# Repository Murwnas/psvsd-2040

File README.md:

# PSVSD 2040

This is a module based on [Yinfanlu's PSVSD adapter](https://github.com/yifanlu/psvsd/). Last year, I took the original Eagle Autodesk files and adapted them to a [KiCad EDA source](https://github.com/Murwnas/psvsd-kicad). This repo code is based on my adaptation. 

One of the problems with the original PSVSD is the out-of-production Genesys chip, which appears to be a generic USB-to-SD bridge that simply exposes Mass Storage. It's theoretically possible to use any such bridge chip in its place, but anyone who has read Yinfanlu's write-up on this will also know that power consumption is the main problem behind those adapters. The PS Vita's modem port never switches off power to the modem port. Therefore, these adapters consume power even when the console is off.

My own fun idea was to recreate this adapter using my favorite chip: The RP2040. It has a USB interface, fast GPIO lines, and very low power consumption---with the potential to go into deep-sleep-like states to draw very small amounts. 

The main downside is USB 1.1 speeds, which theoretically cap at 1.2 MB/s. 

Right now, a board has been designed and fabricated, but I have not had the time to assemble and test it. Whether this is a viable concept will remain to be seen.

Do not attempt to reproduce this unless you are fine with potentially making a faulty board that may or may not fry your PS Vita!

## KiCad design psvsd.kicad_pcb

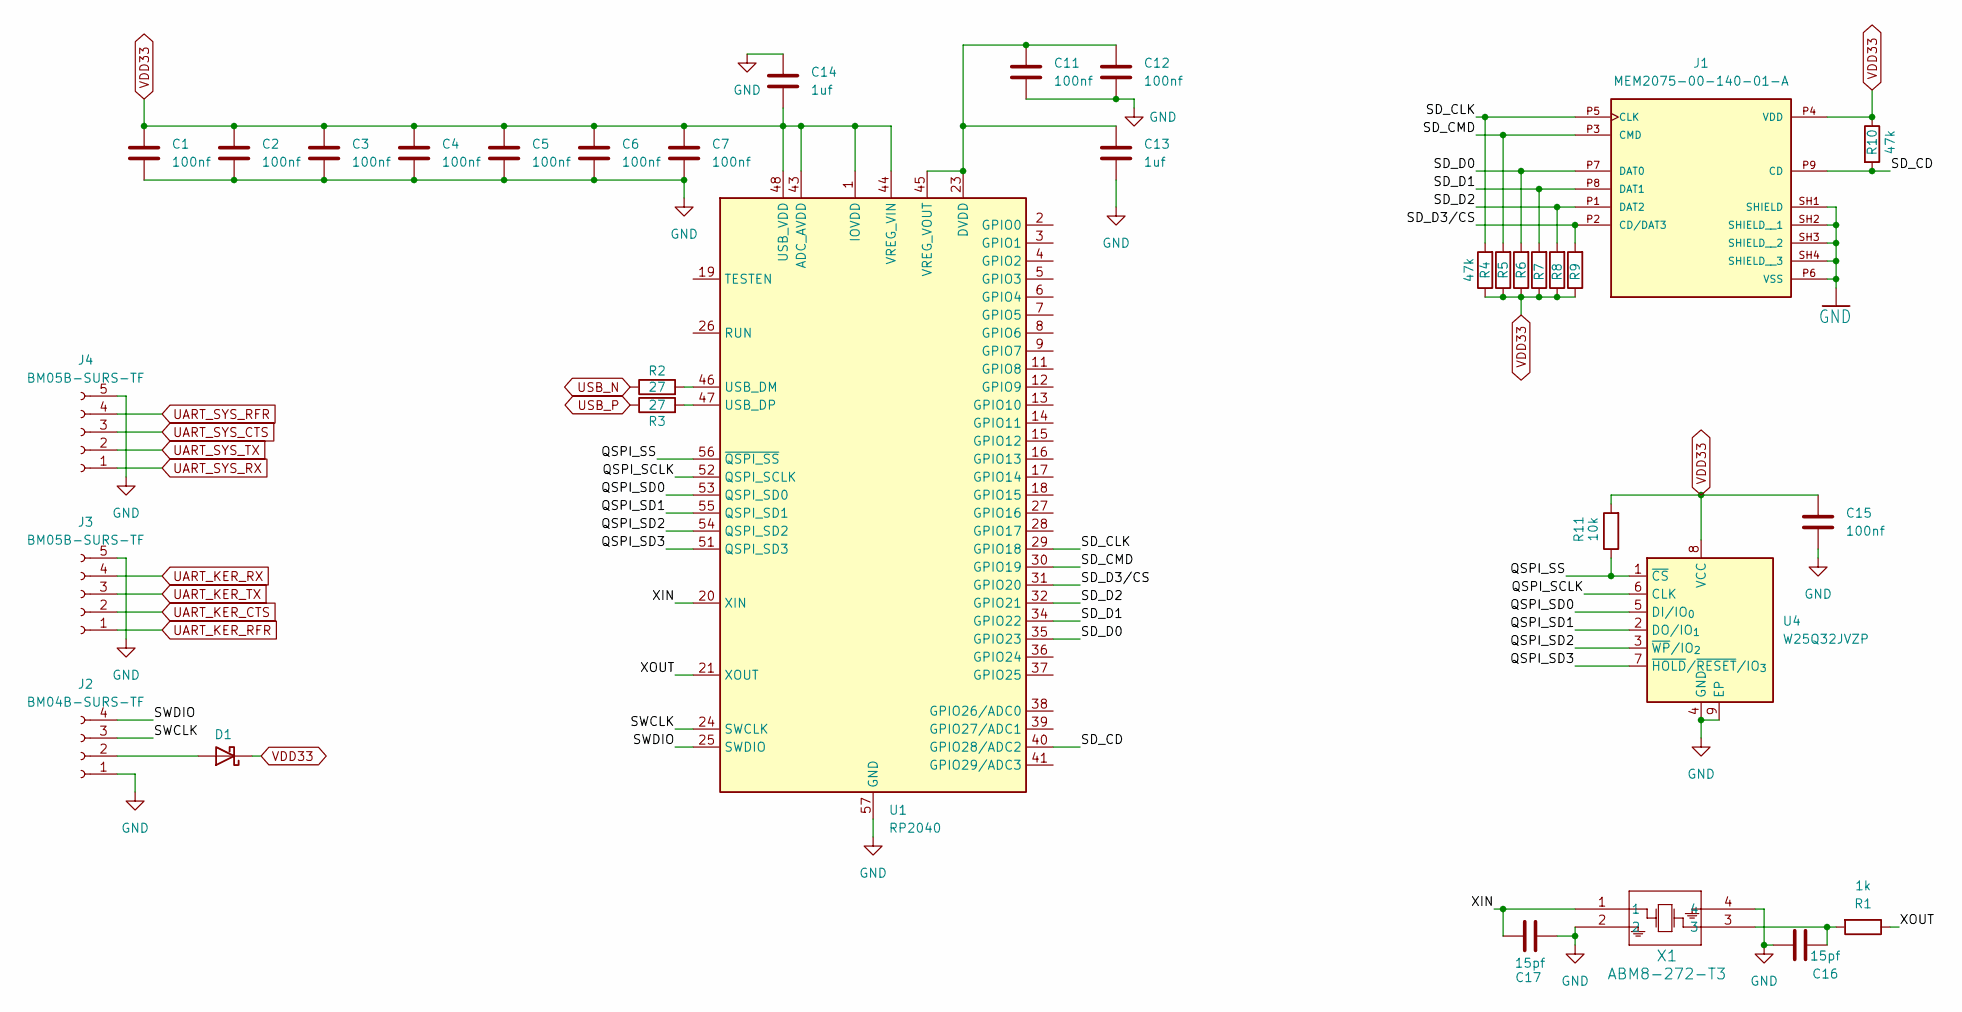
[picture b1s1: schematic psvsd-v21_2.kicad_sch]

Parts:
C1, C2, C3, C4, C5, C6, C7, C11, C12, C15: 100nf; C_0402_1005Metric_Pad0.74x0.62mm_HandSolder
C13, C14: 1uf; C_0402_1005Metric_Pad0.74x0.62mm_HandSolder
C16, C17: 15pf; C_0402_1005Metric_Pad0.74x0.62mm_HandSolder
D1: CD0603-B0340R; D_0603_1608Metric
J1: MEM2075-00-140-01-A; GCT_MEM2075-00-140-01-A; PARTREV A
J2: BM04B-SURS-TF; JST_SUR_BM04B-SURS-TF_1x04-1MP_P0.80mm_Vertical
J3, J4: BM05B-SURS-TF; JST_SUR_BM05B-SURS-TF_1x05-1MP_P0.80mm_Vertical
R1: 1k; R_0402_1005Metric_Pad0.72x0.64mm_HandSolder
R2, R3: 27; R_0402_1005Metric_Pad0.72x0.64mm_HandSolder
R4, R5, R6, R7, R8, R9, R10: 47k; R_0402_1005Metric_Pad0.72x0.64mm_HandSolder
R11: 10k; R_0402_1005Metric_Pad0.72x0.64mm_HandSolder
U1: RP2040; QFN-56-1EP_7x7mm_P0.4mm_EP3.2x3.2mm
U4: W25Q32JVZP; WSON-8-1EP_6x5mm_P1.27mm_EP3.4x4.3mm
X1: ABM8-272-T3; ABM8-272-T3_ABR

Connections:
/psvsd-2040/QSPI_SCLK: U1.52 (QSPI_SCLK), U4.6 (CLK)
/psvsd-2040/QSPI_SD0: U1.53 (QSPI_SD0), U4.5 (DI/IO_{0})
/psvsd-2040/QSPI_SD1: U1.55 (QSPI_SD1), U4.2 (DO/IO_{1})
/psvsd-2040/QSPI_SD2: U1.54 (QSPI_SD2), U4.3 (~WP/IO_{2})
/psvsd-2040/QSPI_SD3: U1.51 (QSPI_SD3), U4.7 (~HOLD/~RESET/IO_{3})
/psvsd-2040/QSPI_SS: R11.1, U1.56 (~QSPI_SS), U4.1 (~CS)
/psvsd-2040/SD_CD: J1.P9 (CD), R10.2, U1.40 (GPIO28/ADC2)
/psvsd-2040/SD_CLK: J1.P5 (CLK), R4.2, U1.29 (GPIO18)
/psvsd-2040/SD_CMD: J1.P3 (CMD), R5.2, U1.30 (GPIO19)
/psvsd-2040/SD_D0: J1.P7 (DAT0), R6.2, U1.35 (GPIO23)
/psvsd-2040/SD_D1: J1.P8 (DAT1), R7.2, U1.34 (GPIO22)
/psvsd-2040/SD_D2: J1.P1 (DAT2), R8.2, U1.32 (GPIO21)
/psvsd-2040/SD_D3/CS: J1.P2 (CD/DAT3), R9.2, U1.31 (GPIO20)
/psvsd-2040/SWCLK: J2.3, U1.24 (SWCLK)
/psvsd-2040/SWDIO: J2.4, U1.25 (SWDIO)
/psvsd-2040/XIN: C17.2, U1.20 (XIN), X1.1
/psvsd-2040/XOUT: R1.1, U1.21 (XOUT)
GND: C1.2, C2.2, C3.2, C4.2, C5.2, C6.2, C7.2, C11.2, C12.2, C13.2, C14.1, C15.2, C16.1, C17.1, J1.P6 (VSS), J1.SH1 (SHIELD), J1.SH2 (SHIELD__1), J1.SH3 (SHIELD__2), J1.SH4 (SHIELD__3), J2.1, J3.5, J4.5, U1.57 (GND), U4.4 (GND), U4.9 (EP), X1.2, X1.4; also elsewhere on the board
unnamed: C16.2, R1.2, X1.3
unnamed: D1.2 (A), J2.2
unnamed: R2.2, U1.46 (USB_DM)
unnamed: R3.2, U1.47 (USB_DP)
unnamed: C11.1, C12.1, C13.1, U1.23 (DVDD), U1.45 (VREG_VOUT), U1.50 (DVDD)
UART_KER_CTS: J3.2; also elsewhere on the board
UART_KER_RFR: J3.1; also elsewhere on the board
UART_KER_RX: J3.4; also elsewhere on the board
UART_KER_TX: J3.3; also elsewhere on the board
UART_SYS_CTS: J4.3; also elsewhere on the board
UART_SYS_RFR: J4.4; also elsewhere on the board
UART_SYS_RX: J4.1; also elsewhere on the board
UART_SYS_TX: J4.2; also elsewhere on the board
USB_N: R2.1; also elsewhere on the board
USB_P: R3.1; also elsewhere on the board
VDD33: C1.1, C2.1, C3.1, C4.1, C5.1, C6.1, C7.1, C14.2, C15.1, D1.1 (K), J1.P4 (VDD), R4.1, R5.1, R6.1, R7.1, R8.1, R9.1, R10.1, R11.2, U1.1 (IOVDD), U1.10 (IOVDD), U1.22 (IOVDD), U1.33 (IOVDD), U1.42 (IOVDD), U1.43 (ADC_AVDD), U1.44 (VREG_VIN), U1.48 (USB_VDD), U1.49 (IOVDD), U4.8 (VCC); also elsewhere on the board

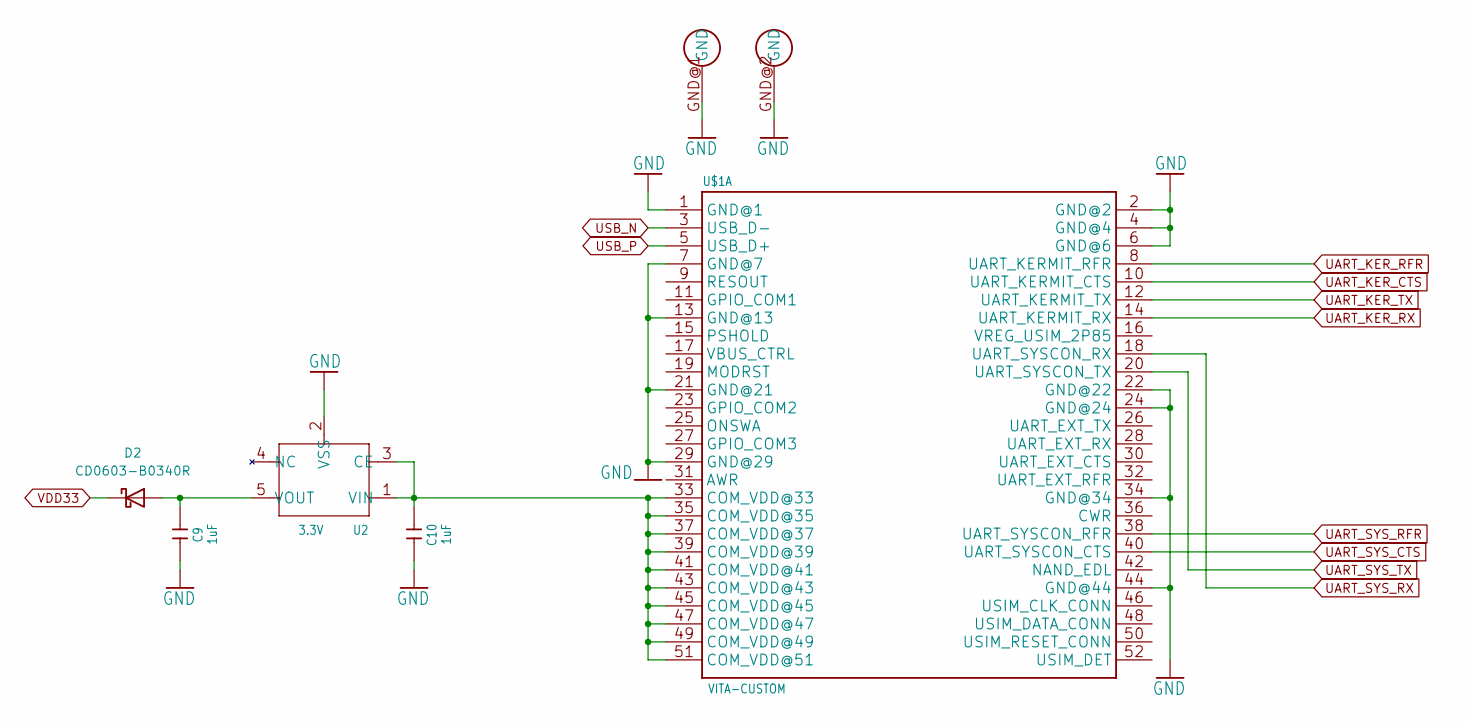
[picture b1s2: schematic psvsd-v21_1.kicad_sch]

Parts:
C9, C10: 1uF; C_0402_1005Metric_Pad0.74x0.62mm_HandSolder
D2: CD0603-B0340R; D_0603_1608Metric
U2: 3.3V; SOT-23-5_470
U$1: VITA-CUSTOM; VITA-MINI-PCI-E

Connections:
GND: C9.2, C10.2, U2.2 (VSS), U$1.1 (GND@1), U$1.2 (GND@2), U$1.4 (GND@4), U$1.6 (GND@6), U$1.7 (GND@7), U$1.13 (GND@13), U$1.21 (GND@21), U$1.22 (GND@22), U$1.24 (GND@24), U$1.29 (GND@29), U$1.34 (GND@34), U$1.44 (GND@44), U$1.GND@1 (GND), U$1.GND@2 (GND); also elsewhere on the board
unnamed: C9.1, D2.2 (A), U2.5 (VOUT)
unnamed: C10.1, U2.1 (VIN), U2.3 (CE), U$1.33 (COM_VDD@33), U$1.35 (COM_VDD@35), U$1.37 (COM_VDD@37), U$1.39 (COM_VDD@39), U$1.41 (COM_VDD@41), U$1.43 (COM_VDD@43), U$1.45 (COM_VDD@45), U$1.47 (COM_VDD@47), U$1.49 (COM_VDD@49), U$1.51 (COM_VDD@51)
UART_KER_CTS: U$1.10 (UART_KERMIT_CTS); also elsewhere on the board
UART_KER_RFR: U$1.8 (UART_KERMIT_RFR); also elsewhere on the board
UART_KER_RX: U$1.14 (UART_KERMIT_RX); also elsewhere on the board
UART_KER_TX: U$1.12 (UART_KERMIT_TX); also elsewhere on the board
UART_SYS_CTS: U$1.40 (UART_SYSCON_CTS); also elsewhere on the board
UART_SYS_RFR: U$1.38 (UART_SYSCON_RFR); also elsewhere on the board
UART_SYS_RX: U$1.18 (UART_SYSCON_RX); also elsewhere on the board
UART_SYS_TX: U$1.20 (UART_SYSCON_TX); also elsewhere on the board
USB_N: U$1.3 (USB_D-); also elsewhere on the board
USB_P: U$1.5 (USB_D+); also elsewhere on the board
VDD33: D2.1 (K); also elsewhere on the board

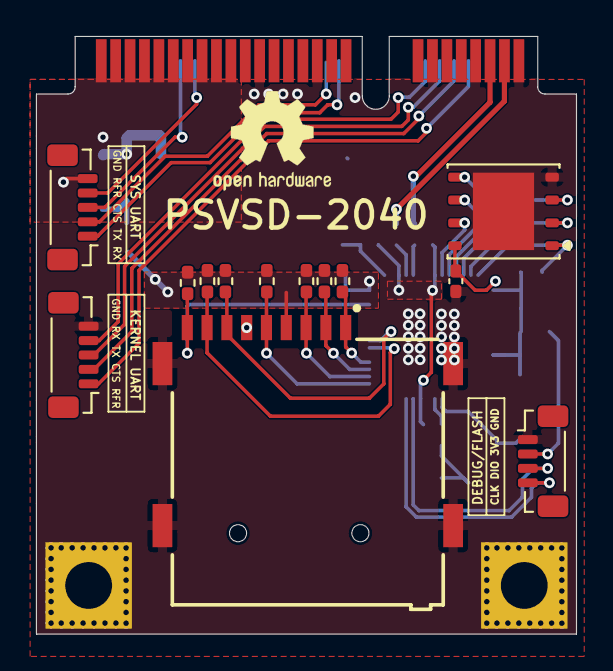
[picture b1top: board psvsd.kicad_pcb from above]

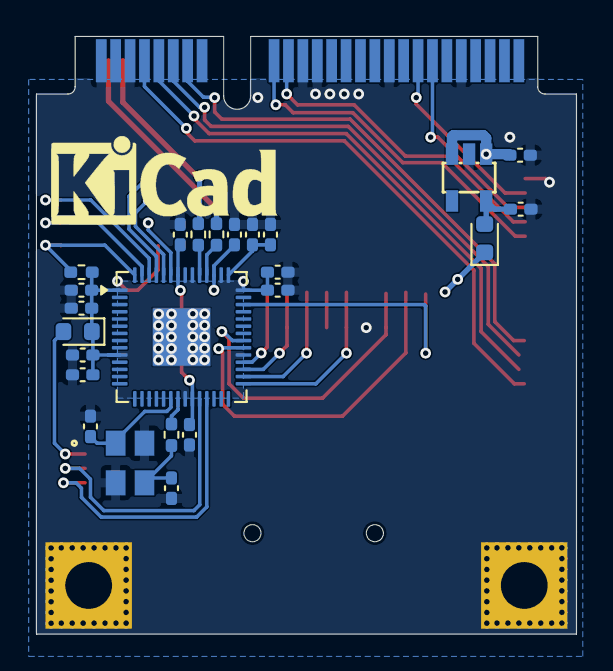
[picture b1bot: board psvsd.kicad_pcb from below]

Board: 2 copper layers, 30.0 x 33.2 mm, 38 parts (24 on the bottom side), 36 nets.
